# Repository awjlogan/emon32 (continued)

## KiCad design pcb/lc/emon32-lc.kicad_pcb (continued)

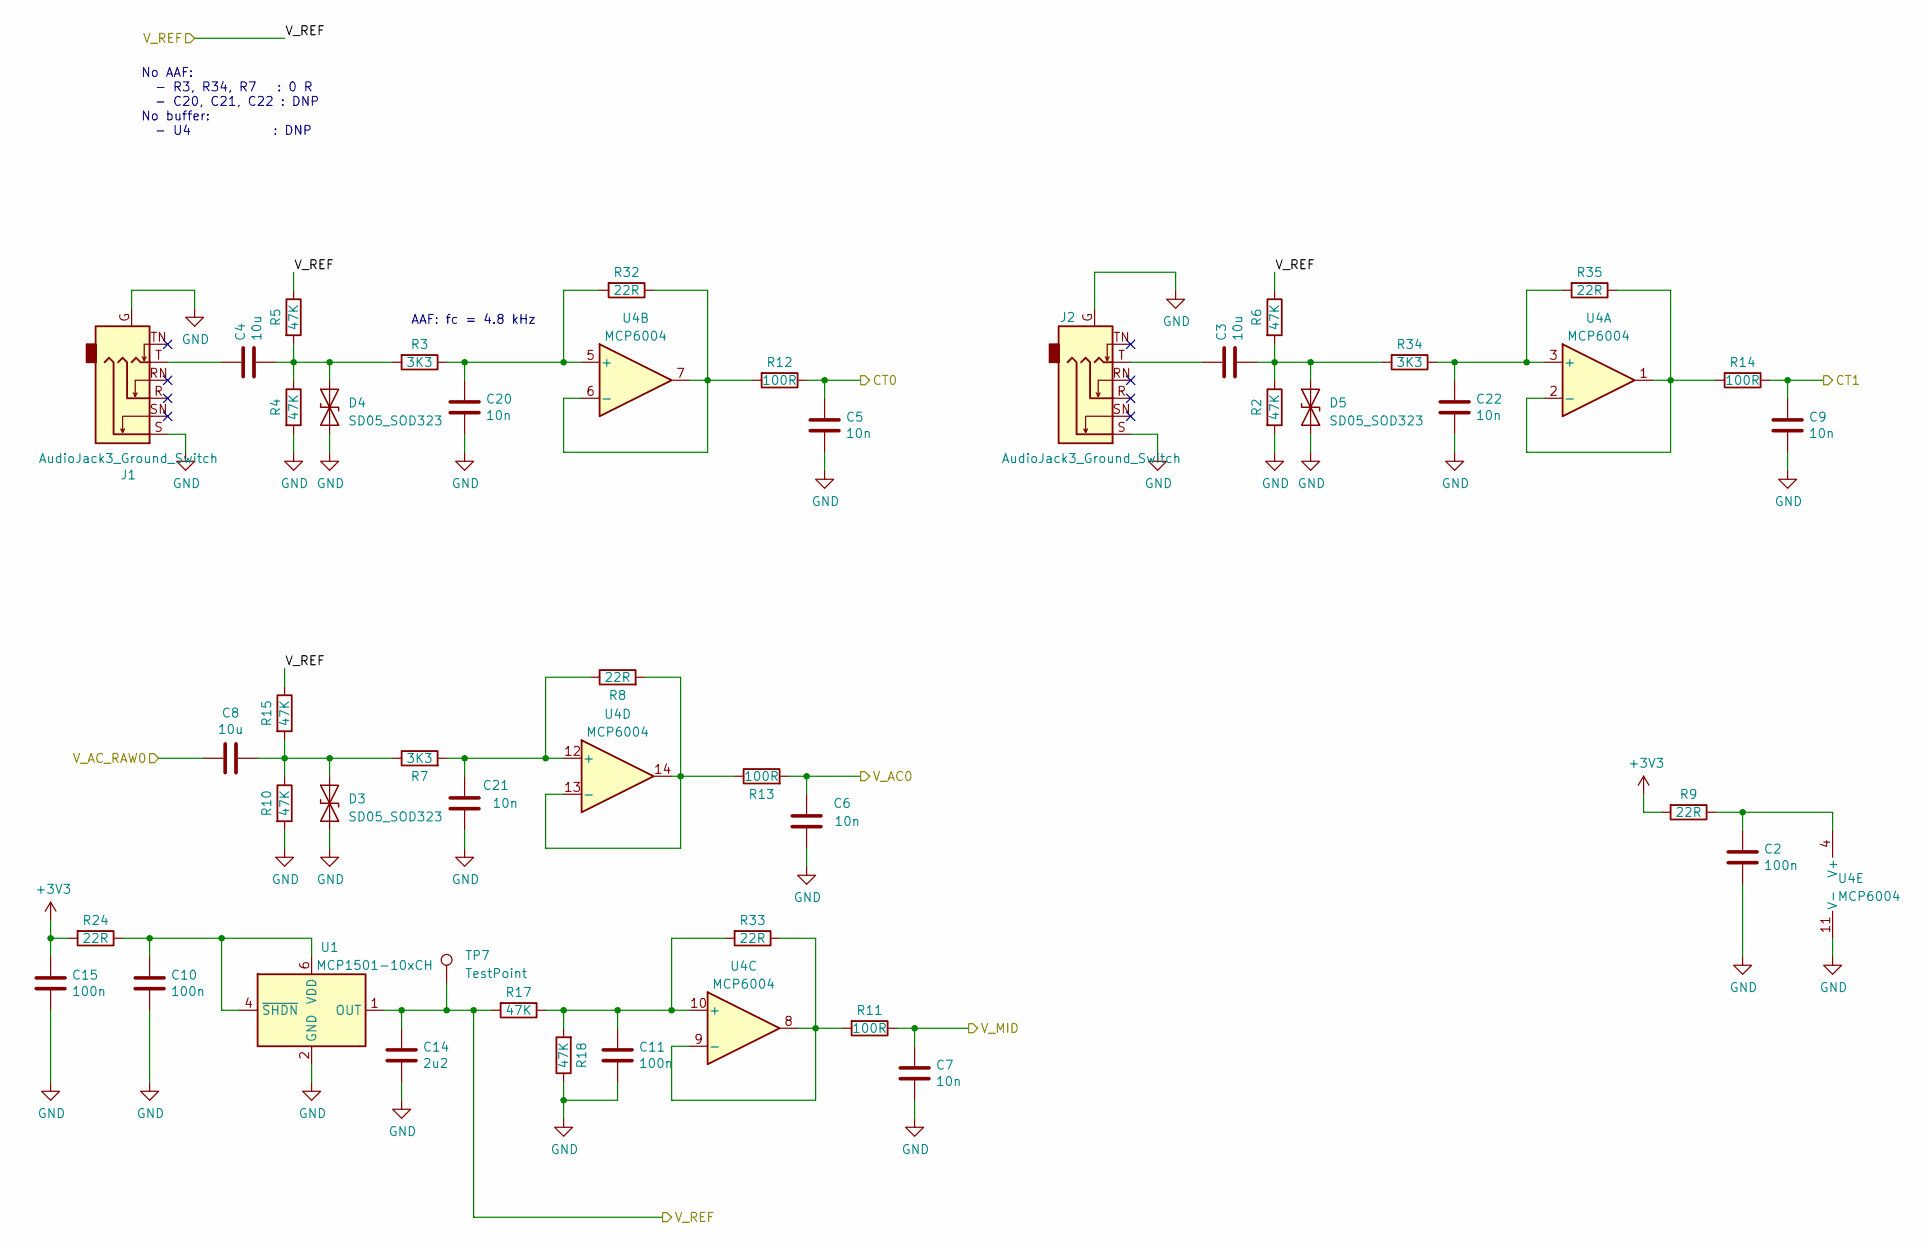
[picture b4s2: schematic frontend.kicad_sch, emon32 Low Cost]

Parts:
C2, C10, C11, C15: 100n; C_0402_1005Metric
C3, C4, C8: 10u; C_0603_1608Metric
C5, C6, C7, C9, C20, C21, C22: 10n; C_0402_1005Metric
C14: 2u2; C_0603_1608Metric_Pad1.08x0.95mm_HandSolder
D3, D4, D5: SD05_SOD323; D_SOD-323
J1, J2: AudioJack3_Ground_Switch; Jack_3.5mm_CUI_SJ-3523-SMT_Horizontal
R2, R4, R5, R6, R10, R15, R17, R18: 47K; R_0402_1005Metric
R3, R7, R34: 3K3; R_0402_1005Metric
R8, R9, R24, R32, R33, R35: 22R; R_0402_1005Metric
R11, R12, R13, R14: 100R; R_0402_1005Metric
TP7: TestPoint; TestPoint_Pad_D1.5mm
U1: MCP1501-10xCH; SOT-23-6
U4: MCP6004; TSSOP-14_4.4x5mm_P0.65mm

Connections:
+3V3: C15.1, R9.2, R24.2; also elsewhere on the board
/I_CHAN_0: C5.2, R12.1; also elsewhere on the board
/I_CHAN_1: C9.2, R14.1; also elsewhere on the board
/V_AC: C6.2, R13.2; also elsewhere on the board
/V_AC_RAW0: C8.2; also elsewhere on the board
/V_MID: C7.1, R11.1; also elsewhere on the board
/V_REF: C14.1, R5.1, R6.1, R15.1, R17.2, TP7.1, U1.1 (OUT); also elsewhere on the board
GND: C2.2, C5.1, C6.1, C7.2, C9.1, C10.2, C11.2, C14.2, C15.2, C20.1, C21.1, C22.1, D3.1 (A1), D4.1 (A1), D5.1 (A1), J1.G, J1.S, J2.G, J2.S, R2.2, R4.2, R10.2, R18.1, U1.2 (GND), U1.3 (GND), U1.5 (GND), U4.11 (V-); also elsewhere on the board
unnamed: C3.2, J2.T
unnamed: C4.2, J1.T
unnamed: C8.1, D3.2 (A2), R7.1, R10.1, R15.2
unnamed: C4.1, D4.2 (A2), R3.2, R4.1, R5.2
unnamed: C3.1, D5.2 (A2), R2.1, R6.2, R34.2
unnamed: C10.1, R24.1, U1.4 (~SHDN), U1.6 (VDD)
unnamed: C22.2, R34.1, R35.2, U4.3 (+)
unnamed: R14.2, R35.1, U4.1, U4.2 (-)
unnamed: C20.2, R3.1, R32.2, U4.5 (+)
unnamed: R12.2, R32.1, U4.6 (-), U4.7
unnamed: C11.1, R17.1, R18.2, R33.2, U4.10 (+)
unnamed: R11.2, R33.1, U4.8, U4.9 (-)
unnamed: C21.2, R7.2, R8.1, U4.12 (+)
unnamed: R8.2, R13.1, U4.13 (-), U4.14
unnamed: C2.1, R9.1, U4.4 (V+)

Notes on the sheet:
AAF: fc = 4.8 kHz
No AAF: - R3, R34, R7 : 0 R - C20, C21, C22 : DNP No buffer: - U4 : DNP

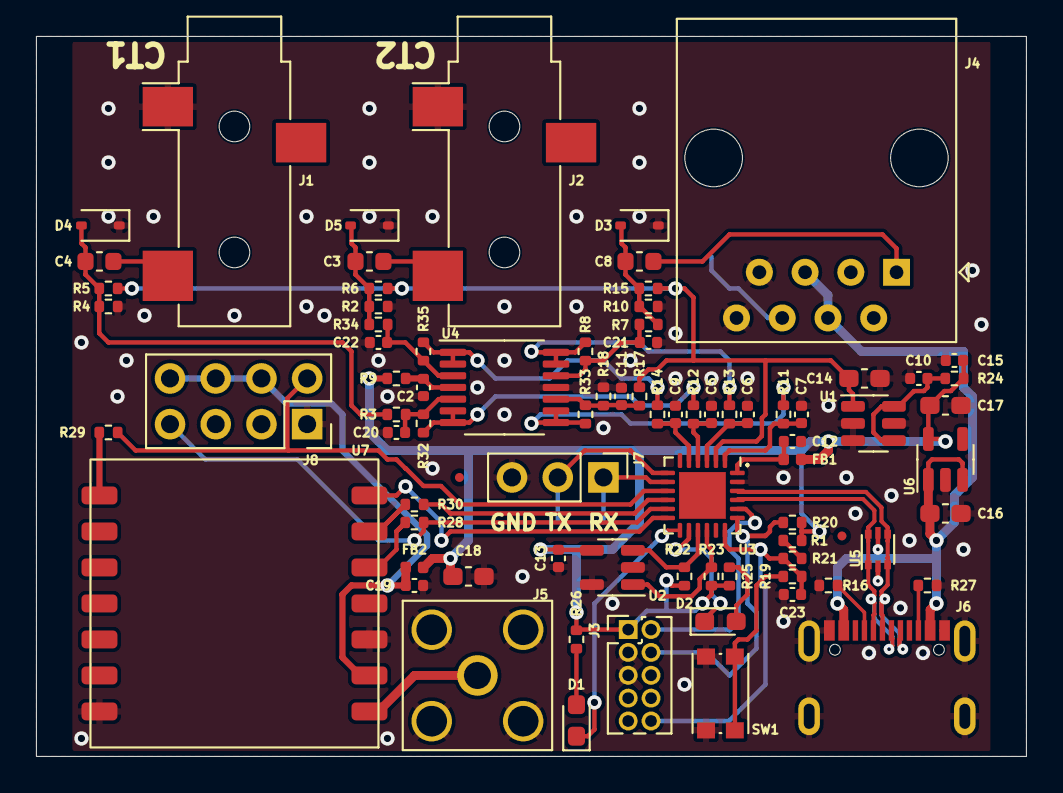
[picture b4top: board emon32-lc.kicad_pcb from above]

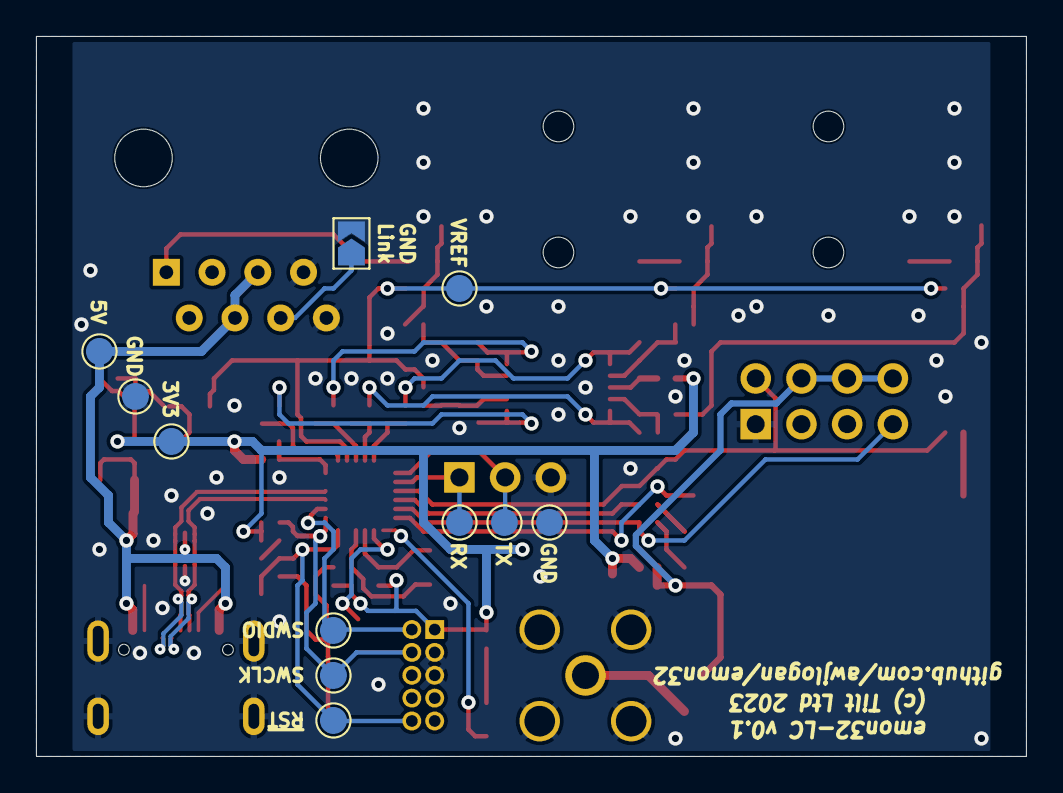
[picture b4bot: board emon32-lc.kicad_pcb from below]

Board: 4 copper layers, 55.0 x 40.0 mm, 92 parts (11 on the bottom side), 52 nets.

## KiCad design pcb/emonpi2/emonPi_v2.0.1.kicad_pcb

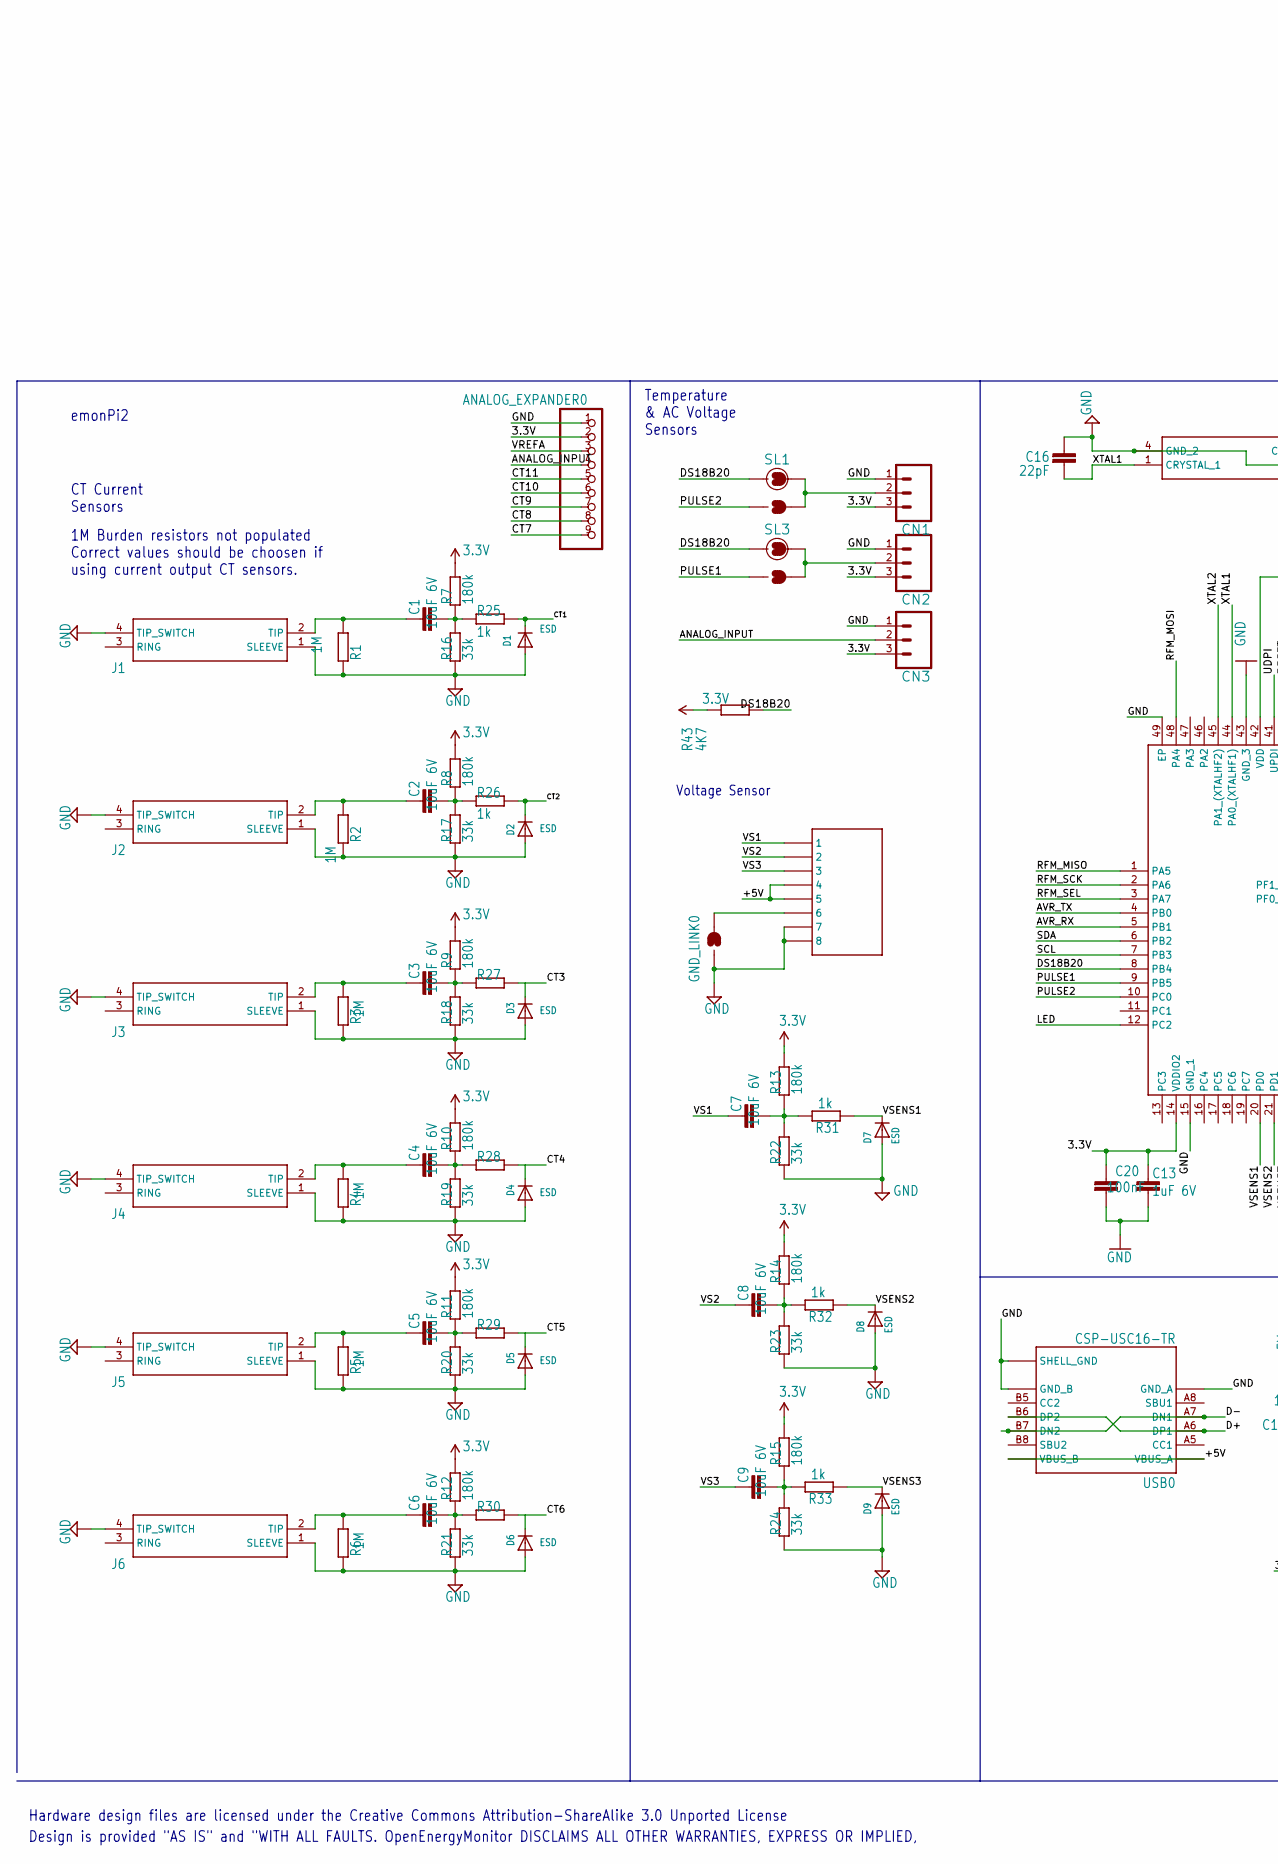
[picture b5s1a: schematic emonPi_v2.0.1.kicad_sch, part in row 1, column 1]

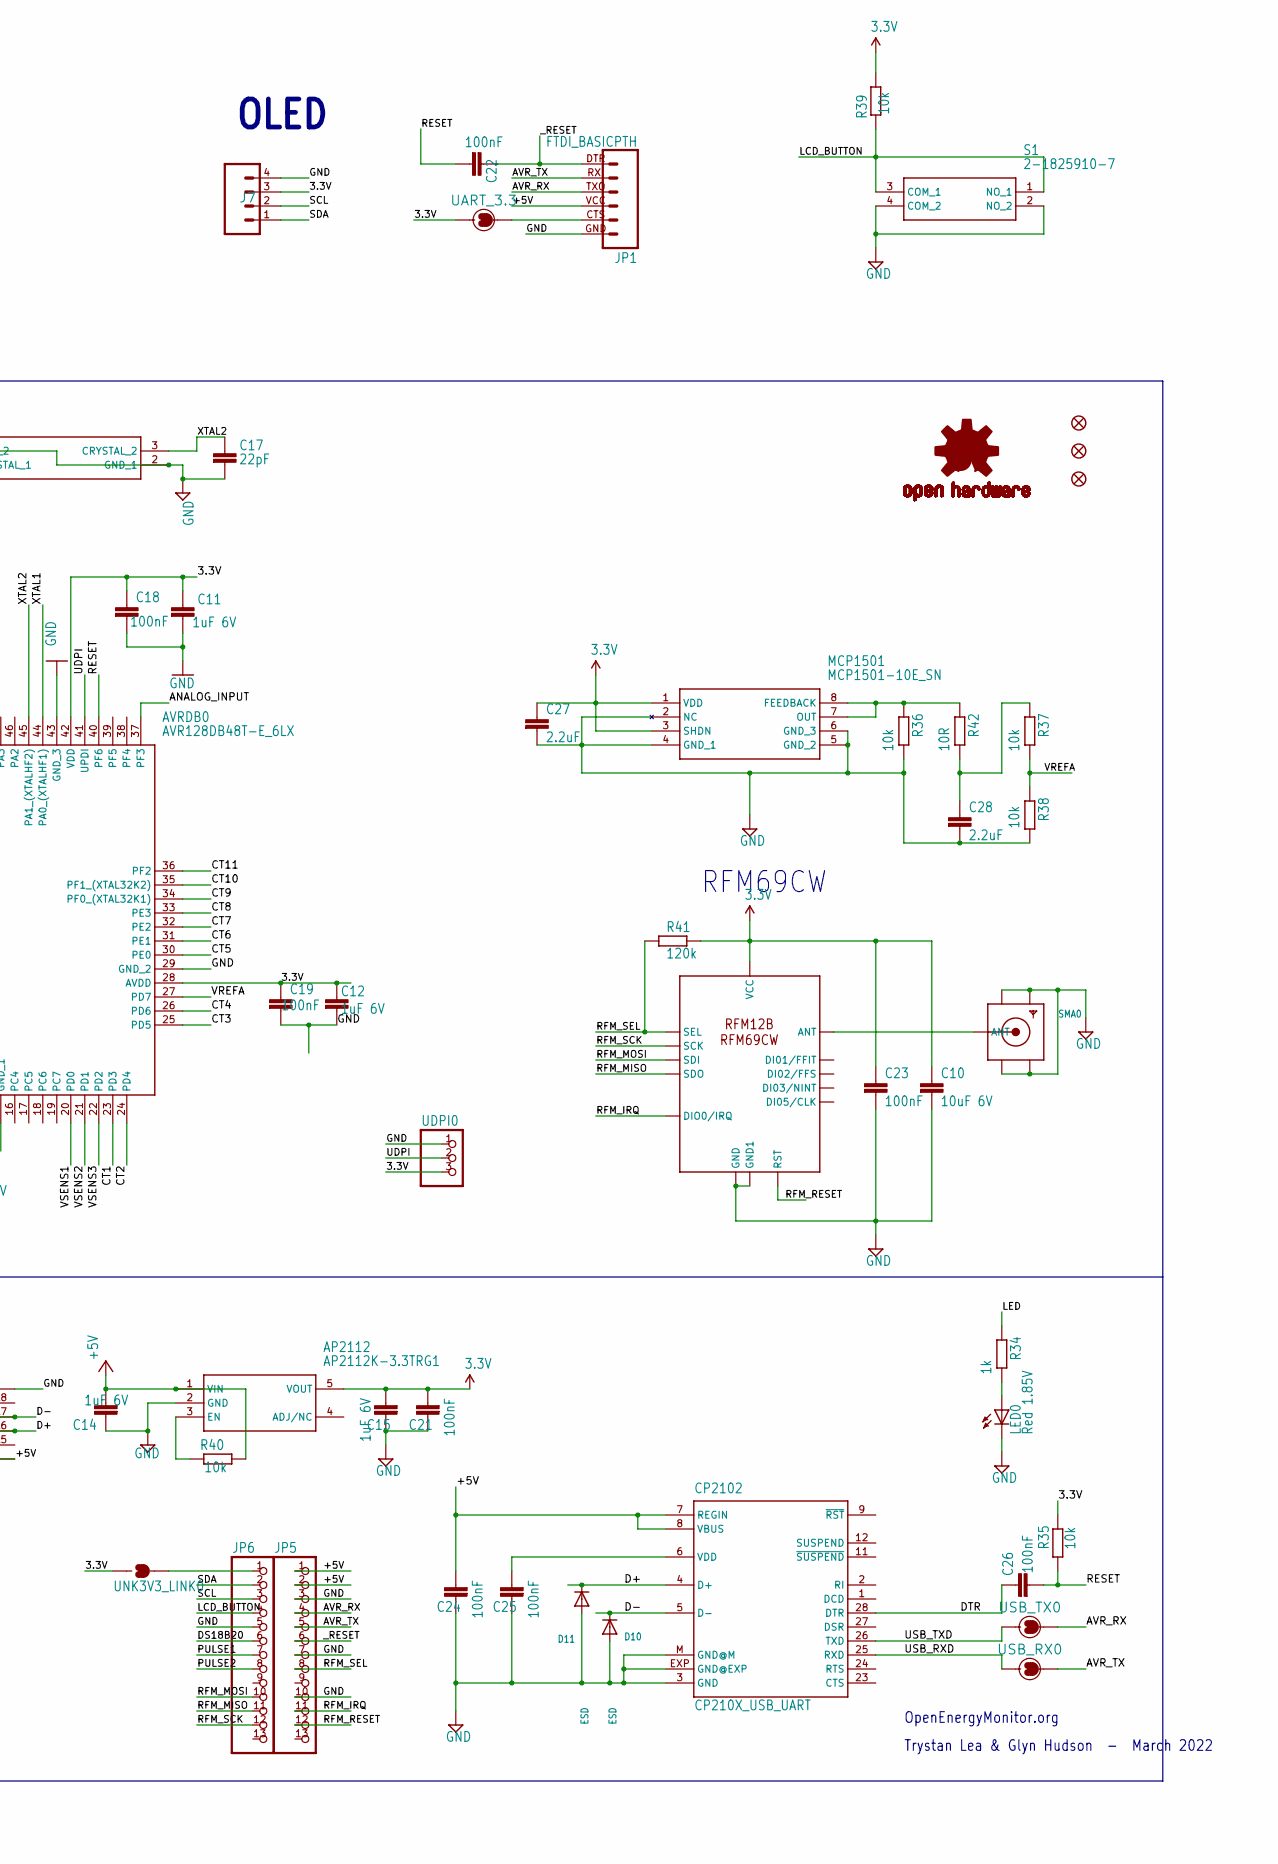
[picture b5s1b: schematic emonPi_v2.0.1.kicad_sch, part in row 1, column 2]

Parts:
ANALOG_EXPANDER0: PINHD-1X9; 1X09-BIG
AP2112: AP2112K-3.3TRG1; SOT95P282X130-5N
AVRDB0: AVR128DB48T-E_6LX; QFN40P600X600X90-49N
C1, C2, C3, C4, C5, C6, C7, C8, C9, C10: 10uF 6V; C0603
C11, C12, C13, C14, C15: 1uF 6V; C0603
C16, C17: 22pF; C0603
C18, C19, C20, C21, C22, C23, C24, C25, C26: 100nF; C0603
C27, C28: 2.2uF; C0603
CN1, CN2, CN3: CONN_03SCREW; SCREWTERMINAL-3.5MM-3
CP2102: CP210X_USB_UART; MLP28
D1, D2, D3, D4, D5, D6, D7, D8, D9, D10, D11: ESD; SOD-523
FD1, FD2, FD3: FIDUCIAL1X2; FIDUCIAL-1X2
GND_LINK0: SOLDERJUMPERNC; SJ_2S
J1, J2, J3, J4, J5, J6: SJ-3524-SMT-TR
J7: CONN_04PTH; 1X04
JP1: FTDI_BASICPTH; FTDI_BASIC
JP5, JP6: PINHD-1X13_BIG; 1X13-BIG
LED0: Red 1.85V; CHIP-LED0805
LOGO1: OSHW-LOGOS-COPPER; OSHW-LOGO-S_COPPER
MCP1501: MCP1501-10E_SN; SOIC127P600X175-8N
R1, R2, R3, R4, R5, R6: 1M; R1206
R7, R8, R9, R10, R11, R12, R13, R14, R15: 180k; R0603
R16, R17, R18, R19, R20, R21, R22, R23, R24: 33k; R0603
R25, R26, R27, R28, R29, R30, R31, R32, R33, R34: 1k; R0603
R35, R36, R37, R38, R39, R40: 10k; R0603
R41: 120k; R0603
R42: 10R; R0603
R43: 4K7; R0603
RFM69: RFM12B/69CW; RFM12B_69CW
RJ45: RJ45-8PTH; RJ45-8
S1: 2-1825910-7; 218259107
SL1, SL3: JUMPER-SMT_2_NC_PASTE_NO-SILK; SMT-JUMPER_2_NC_PASTE_NO-SILK
SL2, SL4: SOLDERJUMPERNC; SJ_2S
SMA0: SMACONNECTOR; SMA90_DIP
UART_3.3: JUMPER-SMT_2_NC_PASTE_NO-SILK; SMT-JUMPER_2_NC_PASTE_NO-SILK
UDPI0: PINHD-1X3; 1X03
UNK3V3_LINK0: SOLDERJUMPERNC; SJ_2S
USB0: CSP-USC16-TR; VALCON_CSP-USC16-TR
USB_RX0: JUMPER-SMT_2_NC_PASTE_NO-SILK; SMT-JUMPER_2_NC_PASTE_NO-SILK
USB_TX0: JUMPER-SMT_2_NC_PASTE_NO-SILK; SMT-JUMPER_2_NC_PASTE_NO-SILK
XTAL0: MCSJK-7U-12.00-12-10-80-B-10; MCSJK7U1200121080B10

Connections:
3.3V: ANALOG_EXPANDER0.2, AP2112.5 (VOUT), AVRDB0.14 (VDDIO2), AVRDB0.28 (AVDD), AVRDB0.42 (VDD), C10.1, C11.1, C12.1, C13.1, C15.2, C18.1, C19.1, C20.1, C21.2, C23.1, C27.1, CN1.3, CN2.3, CN3.3, J7.3, MCP1501.1 (VDD), MCP1501.3 (SHDN), R7.2, R8.2, R9.2, R10.2, R11.2, R12.2, R13.2, R14.2, R15.2, R35.2, R39.1, R41.2, R43.1, RFM69.VDD (VCC), UART_3.3.1, UDPI0.3, UNK3V3_LINK0.1
+5V: AP2112.1 (VIN), C14.2, C24.2, CP2102.7 (REGIN), CP2102.8 (VBUS), JP1.VCC (4), JP5.1, JP5.2, R40.1, RJ45.4, RJ45.5, USB0.A4 (VBUS_A), USB0.A9 (VBUS_A), USB0.B4 (VBUS_B), USB0.B9 (VBUS_B)
ANALOG_INPUT: ANALOG_EXPANDER0.4, AVRDB0.37 (PF3), CN3.2
AVR_RX: AVRDB0.5 (PB1), JP1.TXO (3), JP5.4, USB_TX0.2
AVR_TX: AVRDB0.4 (PB0), JP1.RXI (2), JP5.5, USB_RX0.2
CT1: AVRDB0.23 (PD3), D1.K (C), R25.2
CT2: AVRDB0.24 (PD4), D2.K (C), R26.2
CT3: AVRDB0.25 (PD5), D3.K (C), R27.1
CT4: AVRDB0.26 (PD6), D4.K (C), R28.1
CT5: AVRDB0.30 (PE0), D5.K (C), R29.1
CT6: AVRDB0.31 (PE1), D6.K (C), R30.1
CT7: ANALOG_EXPANDER0.9, AVRDB0.32 (PE2)
CT8: ANALOG_EXPANDER0.8, AVRDB0.33 (PE3)
CT9: ANALOG_EXPANDER0.7, AVRDB0.34 (PF0_(XTAL32K1))
CT10: ANALOG_EXPANDER0.6, AVRDB0.35 (PF1_(XTAL32K2))
CT11: ANALOG_EXPANDER0.5, AVRDB0.36 (PF2)
D+: CP2102.4 (D+), D11.K (C), USB0.A6 (DP1), USB0.B6 (DP2)
D-: CP2102.5 (D-), D10.K (C), USB0.A7 (DN1), USB0.B7 (DN2)
DIG1: RFM69.ANT, SMA0.ANTENNA (ANT)
DS18B20: AVRDB0.8 (PB4), JP6.6, R43.2, SL1.1, SL3.1
DTR: C26.1, CP2102.28 (DTR)
GND: ANALOG_EXPANDER0.1, AP2112.2 (GND), AVRDB0.15 (GND_1), AVRDB0.29 (GND_2), AVRDB0.43 (GND_3), AVRDB0.49 (EP), C10.2, C11.2, C12.2, C13.2, C14.1, C15.1, C16.1, C17.2, C18.2, C19.2, C20.2, C21.1, C23.2, C24.1, C25.1, C27.2, C28.2, CN1.1, CN2.1, CN3.1, CP2102.3 (GND), CP2102.EXP (GND@EXP), CP2102.M (GND@M), D1.A, D2.A, D3.A, D4.A, D5.A, D6.A, D7.A, D8.A, D9.A, D10.A, D11.A, GND_LINK0.1, J1.1 (SLEEVE), J1.4 (TIP_SWITCH), J2.1 (SLEEVE), J2.4 (TIP_SWITCH), J3.1 (SLEEVE), J3.4 (TIP_SWITCH), J4.1 (SLEEVE), J4.4 (TIP_SWITCH), J5.1 (SLEEVE), J5.4 (TIP_SWITCH), J6.1 (SLEEVE), J6.4 (TIP_SWITCH), J7.4, JP1.GND (6), JP5.3, JP5.7, JP5.10, JP6.5, LED0.C, MCP1501.2 (NC), MCP1501.4 (GND_1), MCP1501.5 (GND_2), MCP1501.6 (GND_3), R1.1, R2.1, R3.1, R4.1, R5.1, R6.1, R16.2, R17.2, R18.2, R19.2, R20.2, R21.2, R22.2, R23.1, R24.1, R36.1, R38.1, RFM69.GND, RFM69.GND1, RJ45.7, RJ45.8, S1.2 (NO_2), S1.4 (COM_2), SMA0.GND1, SMA0.GND2, SMA0.GND3, SMA0.GND4, UDPI0.1, USB0.A1 (GND_A), USB0.A12 (GND_A), USB0.B1 (GND_B), USB0.B12 (GND_B), USB0.S1 (SHELL_GND), USB0.S2 (SHELL_GND), USB0.S3 (SHELL_GND), USB0.S4 (SHELL_GND), XTAL0.2 (GND_1), XTAL0.4 (GND_2)
LCD_BUTTON: JP6.4, R39.2, S1.1 (NO_1), S1.3 (COM_1)
LED: AVRDB0.12 (PC2), R34.2
unnamed: C1.1, J1.2 (TIP), R1.2
unnamed: C7.2, R13.1, R22.1, R31.2
unnamed: C3.1, J3.2 (TIP), R3.2
unnamed: C8.2, R14.1, R23.2, R32.2
unnamed: C4.1, J4.2 (TIP), R4.2
unnamed: C9.2, R15.1, R24.2, R33.2
unnamed: C2.1, J2.2 (TIP), R2.2
unnamed: C5.1, J5.2 (TIP), R5.2
unnamed: C5.2, R11.1, R20.1, R29.2
unnamed: C2.2, R8.1, R17.1, R26.1
unnamed: C4.2, R10.1, R19.1, R28.2
unnamed: C1.2, R7.1, R16.1, R25.1
unnamed: C6.1, J6.2 (TIP), R6.2
unnamed: C6.2, R12.1, R21.1, R30.2
unnamed: C3.2, R9.1, R18.1, R27.2
unnamed: CN1.2, SL1.2, SL2.2
unnamed: CN2.2, SL3.2, SL4.2
unnamed: GND_LINK0.2, RJ45.6
unnamed: AP2112.3 (EN), R40.2
unnamed: C28.1, R37.2, R42.1
unnamed: MCP1501.7 (OUT), MCP1501.8 (FEEDBACK), R36.2, R42.2
unnamed: JP6.1, UNK3V3_LINK0.2
unnamed: C25.2, CP2102.6 (VDD)
unnamed: JP1.CTS (5), UART_3.3.2
unnamed: LED0.A, R34.1
PULSE1: AVRDB0.9 (PB5), JP6.7, SL4.1
PULSE2: AVRDB0.10 (PC0), JP6.8, SL2.1
RESET: AVRDB0.40 (PF6), C22.2, C26.2, R35.1
RFM_IRQ: JP5.11, RFM69.IRQ (DIO0/IRQ)
RFM_MISO: AVRDB0.1 (PA5), JP6.11, RFM69.SDO
RFM_MOSI: AVRDB0.48 (PA4), JP6.10, RFM69.SDI
RFM_RESET: JP5.12, RFM69.RST
RFM_SCK: AVRDB0.2 (PA6), JP6.12, RFM69.SCK
RFM_SEL: AVRDB0.3 (PA7), JP5.8, R41.1, RFM69.SEL
SCL: AVRDB0.7 (PB3), J7.2, JP6.3
SDA: AVRDB0.6 (PB2), J7.1, JP6.2
UDPI: AVRDB0.41 (UPDI), UDPI0.2
USB_RXD: CP2102.25 (RXD), USB_RX0.1
USB_TXD: CP2102.26 (TXD), USB_TX0.1
VREFA: ANALOG_EXPANDER0.3, AVRDB0.27 (PD7), R37.1, R38.2
VS1: C7.1, RJ45.1
VS2: C8.1, RJ45.2
VS3: C9.1, RJ45.3
VSENS1: AVRDB0.20 (PD0), D7.K (C), R31.1
VSENS2: AVRDB0.21 (PD1), D8.K (C), R32.1
VSENS3: AVRDB0.22 (PD2), D9.K (C), R33.1
XTAL1: AVRDB0.44 (PA0_(XTALHF1)), C16.2, XTAL0.1 (CRYSTAL_1)
XTAL2: AVRDB0.45 (PA1_(XTALHF2)), C17.1, XTAL0.3 (CRYSTAL_2)
_RESET: C22.1, JP1.DTR (1), JP5.6

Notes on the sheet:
Trystan Lea & Glyn Hudson - March 2022
Temperature & AC Voltage Sensors
RFM69CW
Hardware design files are licensed under the Creative Commons Attribution-ShareAlike 3.0 Unported License
1M Burden resistors not populated Correct values should be choosen if using current output CT sensors.
emonPi2
Design is provided "AS IS" and "WITH ALL FAULTS. OpenEnergyMonitor DISCLAIMS ALL OTHER WARRANTIES, EXPRESS OR IMPLIED,
OpenEnergyMonitor.org
OLED
Voltage Sensor
CT Current Sensors

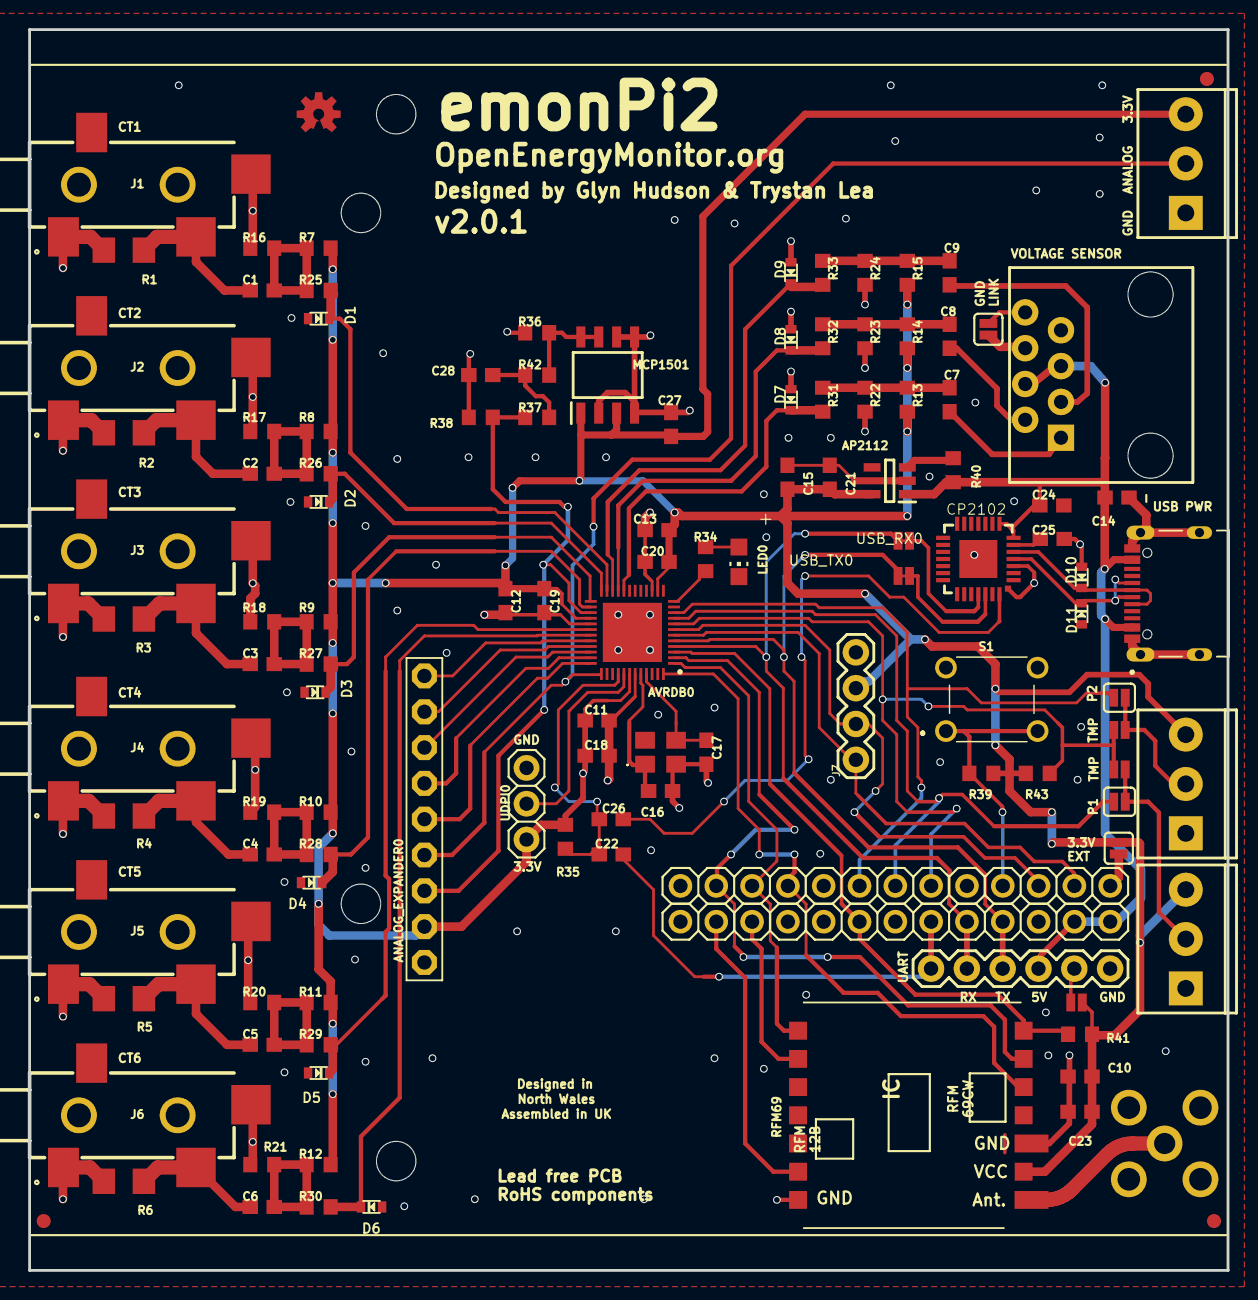
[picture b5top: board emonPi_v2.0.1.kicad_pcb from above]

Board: 2 copper layers, 85.0 x 88.0 mm, 125 parts (0 on the bottom side), 73 nets.

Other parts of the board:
@HOLE0, @HOLE1, @HOLE2, @HOLE3: (no value)

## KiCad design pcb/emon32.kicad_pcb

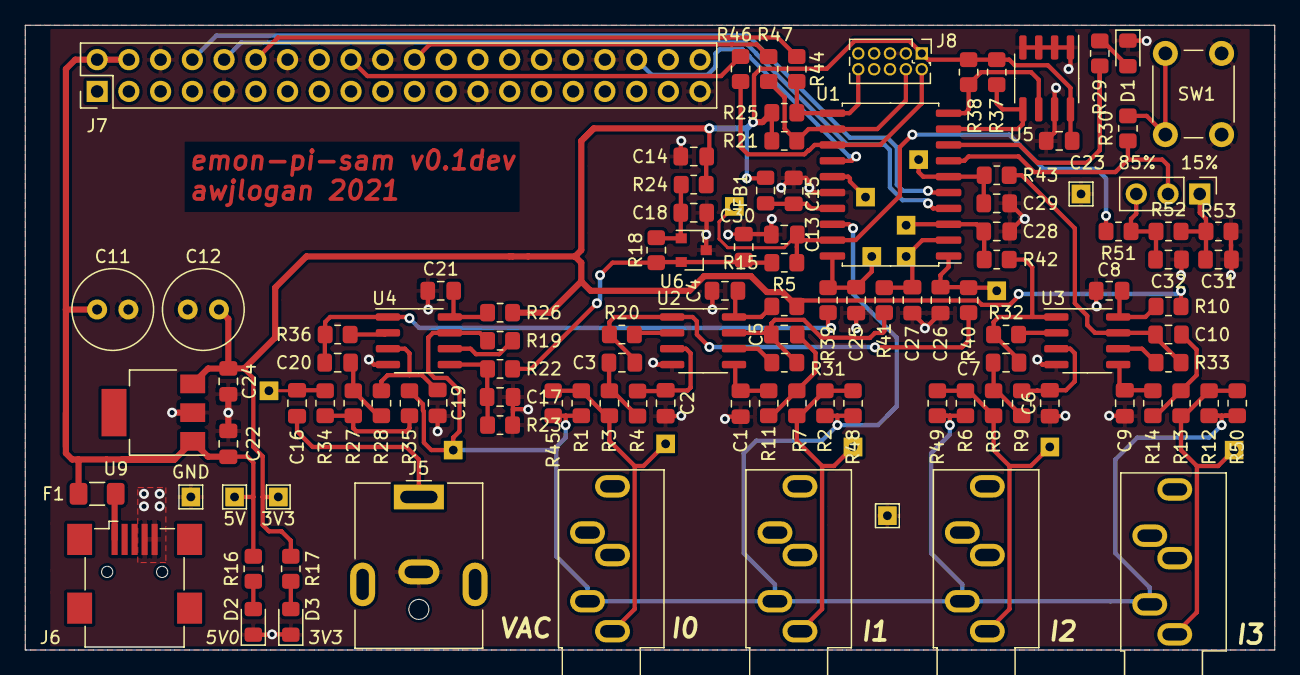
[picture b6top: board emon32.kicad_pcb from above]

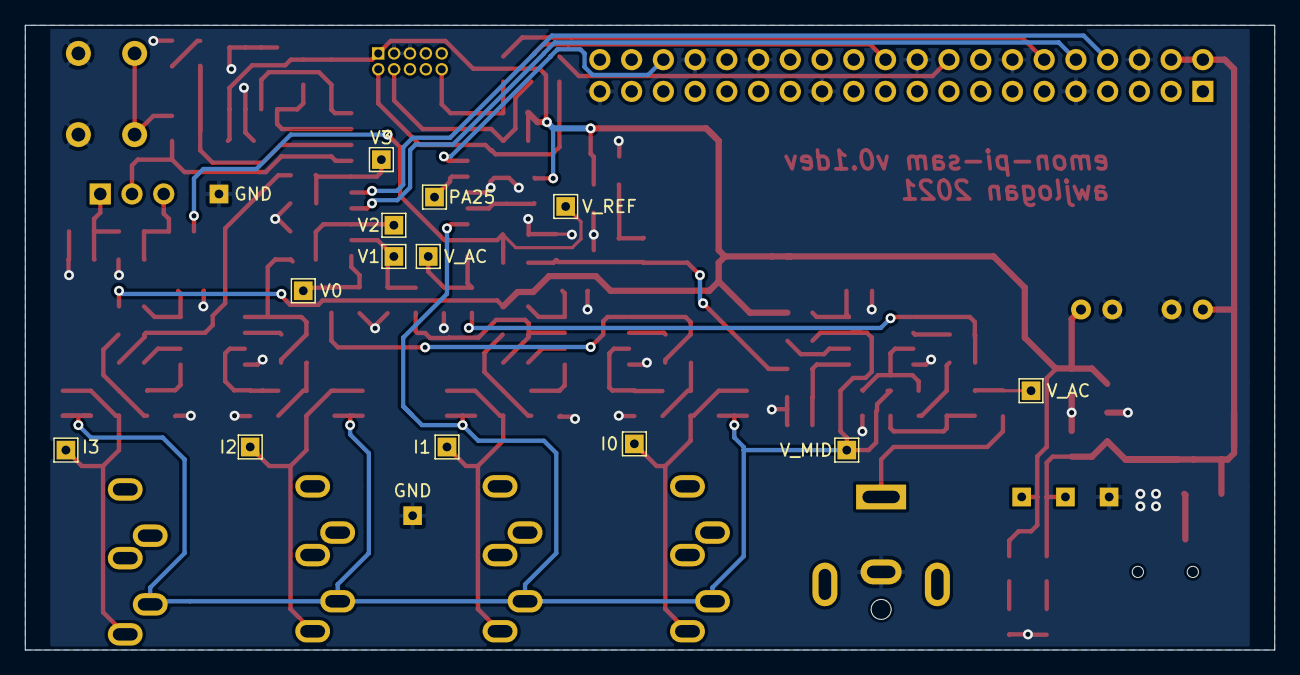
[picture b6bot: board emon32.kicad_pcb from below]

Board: 2 copper layers, 100.0 x 50.0 mm, 125 parts (13 on the bottom side), 66 nets.

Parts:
C1, C2, C6, C9, C19: 4n7; C_0805_2012Metric_Pad1.18x1.45mm_HandSolder
C3, C5, C7, C10, C20, C25, C26, C27, C28, C29: 10n; C_0805_2012Metric_Pad1.18x1.45mm_HandSolder
C4, C8, C13, C14, C15, C17, C18, C21, C23, C31, C32: 100n; C_0805_2012Metric_Pad1.18x1.45mm_HandSolder
C11, C12: 10u; C_Radial_D6.3mm_H5.0mm_P2.50mm
C16: 1u; C_0805_2012Metric_Pad1.18x1.45mm_HandSolder
C22, C24, C30: 2u2; C_0805_2012Metric_Pad1.18x1.45mm_HandSolder
D1, D2, D3: LED; LED_0805_2012Metric_Pad1.15x1.40mm_HandSolder
F1: Fuse; Fuse_1206_3216Metric_Pad1.42x1.75mm_HandSolder
FB1: FerriteBead_Small; L_0805_2012Metric_Pad1.15x1.40mm_HandSolder
J1, J2, J3, J4: AudioJack3_Ground_Switch; Jack_3.5mm_CUI_SJ1-3535NG_Horizontal
J5: Jack-DC; BarrelJack_CUI_PJ-063AH_Horizontal
J6: USB_B; USB_Mini-B_Wuerth_65100516121_Horizontal
J7: Raspberry_Pi_2_3; PinHeader_2x20_P2.54mm_Vertical
J8: Conn_02x05_Odd_Even; PinHeader_2x05_P1.27mm_Vertical
J9: Conn_01x03_Male; PinHeader_1x03_P2.54mm_Vertical
R1, R2, R6, R12, R45, R48, R49, R50: 22R; R_0805_2012Metric_Pad1.20x1.40mm_HandSolder
R3, R7, R8, R13, R27: 24K; R_0805_2012Metric_Pad1.20x1.40mm_HandSolder
R4, R9, R11, R14, R28: 15K; R_0805_2012Metric_Pad1.20x1.40mm_HandSolder
R5, R10, R15, R24, R26: 10R; R_0805_2012Metric_Pad1.20x1.40mm_HandSolder
R16, R17, R29, R30: 330R; R_0805_2012Metric_Pad1.20x1.40mm_HandSolder
R18, R19, R20, R31, R32, R33, R36, R39, R40, R41, R42, R43: 0R; R_0805_2012Metric_Pad1.20x1.40mm_HandSolder
R21, R44, R46, R47: 1K; R_0805_2012Metric_Pad1.20x1.40mm_HandSolder
R22, R23, R34, R35, R52: 47K; R_0805_2012Metric_Pad1.20x1.40mm_HandSolder
R25, R51, R53: 10K; R_0805_2012Metric_Pad1.20x1.40mm_HandSolder
R37, R38: 3K3; R_0805_2012Metric_Pad1.20x1.40mm_HandSolder
SW1: SW_Push; SW_PUSH_6mm
TP1: 5V; TestPoint_THTPad_1.5x1.5mm_Drill0.7mm
TP2: 3V3; TestPoint_THTPad_1.5x1.5mm_Drill0.7mm
TP3, TP7: Ix_RAW; TestPoint_THTPad_1.5x1.5mm_Drill0.7mm
TP4, TP8: Iy_RAW; TestPoint_THTPad_1.5x1.5mm_Drill0.7mm
TP5, TP9: Vx; TestPoint_THTPad_1.5x1.5mm_Drill0.7mm
TP6, TP10: Vy; TestPoint_THTPad_1.5x1.5mm_Drill0.7mm
TP11: VAC_RAW; TestPoint_THTPad_1.5x1.5mm_Drill0.7mm
TP13: VAC; TestPoint_THTPad_1.5x1.5mm_Drill0.7mm
TP14: VMID_BUF; TestPoint_THTPad_1.5x1.5mm_Drill0.7mm
TP15: VREF; TestPoint_THTPad_1.5x1.5mm_Drill0.7mm
TP16, TP17, TP18: GND; TestPoint_THTPad_1.5x1.5mm_Drill0.7mm
TP20: PA25; TestPoint_THTPad_1.5x1.5mm_Drill0.7mm
U1: ATSAMD11D14A-SS; SOIC-20W_7.5x12.8mm_P1.27mm
U2, U3, U4: MCP6002-xSN; SOIC-8_3.9x4.9mm_P1.27mm
U5: 24LC08; SOIC-8_3.9x4.9mm_P1.27mm
U6: REF3012; SOT-23
U9: MCP1825S; SOT-223

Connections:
+3V3: C12.1, C14.1, C23.1, C24.1, FB1.1, J8.1, R5.2, R10.2, R17.1, R21.1, R24.2, R25.1, R26.2, R37.1, R38.1, TP2.1, U5.8 (VCC), U9.3 (VO)
+5V: C11.1, C22.1, F1.1, J7.2 (5V), J7.4 (5V), R16.1, TP1.1, U9.1 (VI)
/EXTINT: J7.36 (GPIO16), U1.14 (PA24)
/I_CHAN_0: C26.2, R40.1, TP5.1, U1.1 (PA05)
/I_CHAN_1: C27.2, R41.1, TP6.1, U1.2 (PA06)
/I_CHAN_2: C28.2, R42.1, TP9.1, U1.3 (PA07)
/I_CHAN_3: C29.2, R43.1, TP10.1, U1.6 (PA14)
/LED: R29.1, U1.8 (PA16)
/SCL: R38.2, U1.10 (PA23), U5.6 (SCL)
/SDA: R37.2, U1.9 (PA22), U5.5 (SDA)
/SW: J9.2, R30.1, U1.7 (PA15)
/SWCLK: J8.4, R21.2, R47.2, U1.12 (PA30/SWCLK)
/SWDIO: J8.2, R46.2, U1.13 (PA31/SWDIO)
/UART_RX: J7.8 (GPIO14/TXD), U1.5 (PA09/XOUT)
/UART_TX: J7.10 (GPIO15/RXD), U1.4 (PA08/XIN)
/V_0.15: C31.1, J9.1, R52.2, R53.1
/V_0.85: C32.1, J9.3, R51.2, R52.1
/V_AC: C25.2, R39.2, TP13.1, U1.20 (PA04)
/V_MID: J1.T, J2.T, J3.T, J4.T, R1.1, R2.1, R6.1, R12.1, R19.1, R35.2, R45.1, R48.1, R49.1, R50.1, TP14.1, U1.18 (PA02), U4.7
/V_REF: C13.1, R15.1, R51.1, TP15.1, U1.19 (PA03)
/~RST: J8.10, R25.2, R44.2, U1.11 (PA28/~RST)
GND: C1.1, C2.1, C4.1, C6.1, C8.1, C9.1, C11.2, C12.2, C13.2, C14.2, C15.2, C17.2, C18.2, C19.2, C21.2, C22.2, C23.2, C24.2, C25.1, C26.1, C27.1, C28.1, C29.1, C30.2, C31.2, C32.2, D1.1 (K), D2.1 (K), D3.1 (K), J5.2, J6.4 (GND), J6.5 (Shield), J7.6 (GND), J7.9 (GND), J7.14 (GND), J7.20 (GND), J7.25 (GND), J7.30 (GND), J7.34 (GND), J7.39 (GND), J8.3, J8.5, R23.1, R53.2, SW1.2, TP16.1, TP17.1, TP18.1, U1.16 (GND), U2.4 (V-), U3.4 (V-), U4.4 (V-), U5.1 (A0), U5.2 (A1), U5.3 (A2), U5.4 (GND), U5.7 (WP), U6.3 (GND), U9.2 (GND)
unnamed: C1.2, R11.1, U2.5 (+)
unnamed: C2.2, R4.1, U2.3 (+)
unnamed: C3.1, R3.1, R4.2
unnamed: C3.2, R20.1, R40.2, U2.1
unnamed: C4.2, R5.1, U2.8 (V+)
unnamed: C5.1, R7.1, R11.2
unnamed: C5.2, R31.1, R41.2, U2.7
unnamed: C6.2, R9.1, U3.3 (+)
unnamed: C7.1, R8.1, R9.2
unnamed: C7.2, R32.1, R42.2, U3.1
unnamed: C8.2, R10.1, U3.8 (V+)
unnamed: C9.2, R14.1, U3.5 (+)
unnamed: C10.1, R13.1, R14.2
unnamed: C10.2, R33.1, R43.2, U3.7
unnamed: C15.1, FB1.2, U1.17 (VDD)
unnamed: C16.1, R34.1, TP11.1
unnamed: C16.2, J5.1
unnamed: C17.1, R22.1, R23.2, U4.5 (+)
unnamed: C18.1, R18.2, R24.1, U6.1 (IN)
unnamed: C19.1, R28.2, U4.3 (+)
unnamed: C20.1, R36.1, R39.1, U4.1
unnamed: C20.2, R27.2, R28.1
unnamed: C21.1, R26.1, U4.8 (V+)
unnamed: C30.1, R15.2, R18.1, R22.2, U6.2 (OUT)
unnamed: D1.2 (A), R29.2
unnamed: D2.2 (A), R16.2
unnamed: D3.2 (A), R17.2
unnamed: F1.2, J6.1 (VBUS)
unnamed: J1.S, R1.2, R3.2, R45.2, TP3.1
unnamed: J2.S, R6.2, R8.2, R49.2, TP7.1
unnamed: J3.S, R2.2, R7.2, R48.2, TP4.1
unnamed: J4.S, R12.2, R13.2, R50.2, TP8.1
unnamed: J7.12 (GPIO18/PWM0), R44.1
unnamed: J7.18 (GPIO24), R46.1
unnamed: J7.22 (GPIO25), R47.1
unnamed: R19.2, U4.6 (-)
unnamed: R20.2, U2.2 (-)
unnamed: R27.1, R34.2, R35.1
unnamed: R30.2, SW1.1
unnamed: R31.2, U2.6 (-)
unnamed: R32.2, U3.2 (-)
unnamed: R33.2, U3.6 (-)
unnamed: R36.2, U4.2 (-)
unnamed: TP20.1, U1.15 (PA25)

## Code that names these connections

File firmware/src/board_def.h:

#ifndef BOARD_DEF_H
#define BOARD_DEF_H

/* This file contains defines specific to the board that is being used. To
 * extend this, the base SAMD10 configuration can be bracketed in IFDEF
 */

/* Online configuration takes around 2.5 KB of flash. Comment out this define to
 * save space, with only RO access to configuration values.
 */
#define CONFIGURATION_RW

/* Clock frequencies
 *  - Core is on the 48 MHz DFLL
 *  - Peripherals are on the OSC8M / 8 -> MHz
 */
#define F_CORE              48000000ul
#define F_PERIPH            8000000ul
#define F_TC1               F_PERIPH / 8
#define F_TC2               F_PERIPH / 8

/* Analog comparator (AC) for zero crossing detection. Uncomment if the AC is
 * being used for zero crossing. If not present, a software routine is used
 */
/* #define ZERO_CROSSING_HW */

/* EEPROM */
/* Uncomment to use the software EEPROM mode (not implemented yet)
 * #define EEPROM_EMULATED
 */
/* Top of EEPROM address, not including R/W bit */
#define EEPROM_BASE_ADDR    0x50
/* Maximum number of bytes in a single page */
#define EEPROM_PAGE_SIZE    16u
/* Worst case EEPROM write time (microseconds) */
#define EEPROM_WR_TIME      5000ul
/* Size (bytes) of EEPROM */
#define EEPROM_SIZE_BYTES   512u
/* Size (bytes) of wear levelled portion */
#define EEPROM_WL_SIZE      384u
/* Offset of wear levelled area */
#define EEPROM_WL_OFFSET    (EEPROM_SIZE_BYTES - EEPROM_WL_SIZE)

/* SERCOM peripheral defines */
#define SERCOM_UART_DBG             SERCOM0
#define SERCOM_I2CM                 SERCOM1
#define SERCOM_UART_DATA            SERCOM2
#define SERCOM_SPI_DATA             SERCOM2

#define SERCOM_UART_DBG_APBCMASK    PM_APBCMASK_SERCOM0
#define SERCOM_I2CM_APBCMASK        PM_APBCMASK_SERCOM1
#define SERCOM_UART_DATA_APBCMASK   PM_APBCMASK_SERCOM2

#define SERCOM_UART_DBG_GCLK_ID     SERCOM0_GCLK_ID_CORE
#define SERCOM_I2CM_GCLK_ID         SERCOM1_GCLK_ID_CORE
#define SERCOM_UART_DATA_GCLK_ID    SERCOM2_GCLK_ID_CORE

#define SERCOM_UART_DBG_DMAC_ID_TX  SERCOM0_DMAC_ID_TX
#define SERCOM_I2CM_DMAC_ID_TX      SERCOM2_DMAC_ID_TX
#define SERCOM_I2CM_DMAC_ID_RX      SERCOM2_DMAC_ID_RX
#define SERCOM_UART_DATA_DMAC_ID_TX SERCOM2_DMAC_ID_TX

#define SERCOM_UART_DBG_NVIC_IRQn   SERCOM0_IRQn

/* Pulse counting */
#define PULSE_MIN_PERIOD_MS         100u    /* Minimum period between pulses */
#define PULSE_EIC_MAP               3u
#define PULSE_EIC_FILTER            EIC_CONFIG_FILTEN3
#define PULSE_EIC_RISING            EIC_CONFIG_SENSE3_RISE
#define PULSE_EIC_INTFLAG           EIC_INTFLAG_EXTINT3
#define PULSE_EIC_INTENSET          EIC_INTENSET_EXTINT3
#define PULSE_EIC_INTENCLR          EIC_INTENCLR_EXTINT3

/* Pin assignments (nb. logical, not physical) */
#define PIN_EXTINT          24u
#define PIN_GEN_STATUS      25u
#define PIN_LED             16u
#define PIN_SW              15u
#define PIN_UART_DBG_RX     9u
#define PIN_UART_DBG_TX     8u
#define PIN_I2C_SDA         22u
#define PIN_I2C_SCL         23u

/* Debug UART related defines */
#define UART_DBG_PAD_RX     3u
#define UART_DBG_PAD_TX     1u
#define UART_DBG_BAUD       38400u

/* SPI related defines */
#define PIN_SPI_MISO        14u
#define PIN_SPI_MOSI        15u
#define PIN_SPI_SCK         16u
#define PIN_SPI_RFM_SS      17u
#define SPI_DATA_BAUD       4000000ul

/* DMA defines */
#define NUM_CHAN_DMA        4u
#define DMA_CHAN_UART_DATA  3u
#define DMA_CHAN_I2CM       2u
#define DMA_CHAN_UART_DBG   1u
#define DMA_CHAN_ADC        0u

/* SAMD10 calibration values (NVM User Row Mapping Table 9-3) */
#define CAL_REG_LOW         *(const volatile uint32_t *)(0x00806020)
#define CAL_REG_HIGH        *(const volatile uint32_t *)(0x00806024)
#define CAL_OSC32_Msk       0x1FC0u
#define CAL_OSC32_Pos       6u
#define CAL_ADC_BIAS_Msk    0x38u
#define CAL_ADC_BIAS_Pos    3u
#define CAL_ADC_LIN_L_Msk   0xF800u
#define CAL_ADC_LIN_L_Pos   27u
#define CAL_ADC_LIN_H_Msk   0x7u

#endif
